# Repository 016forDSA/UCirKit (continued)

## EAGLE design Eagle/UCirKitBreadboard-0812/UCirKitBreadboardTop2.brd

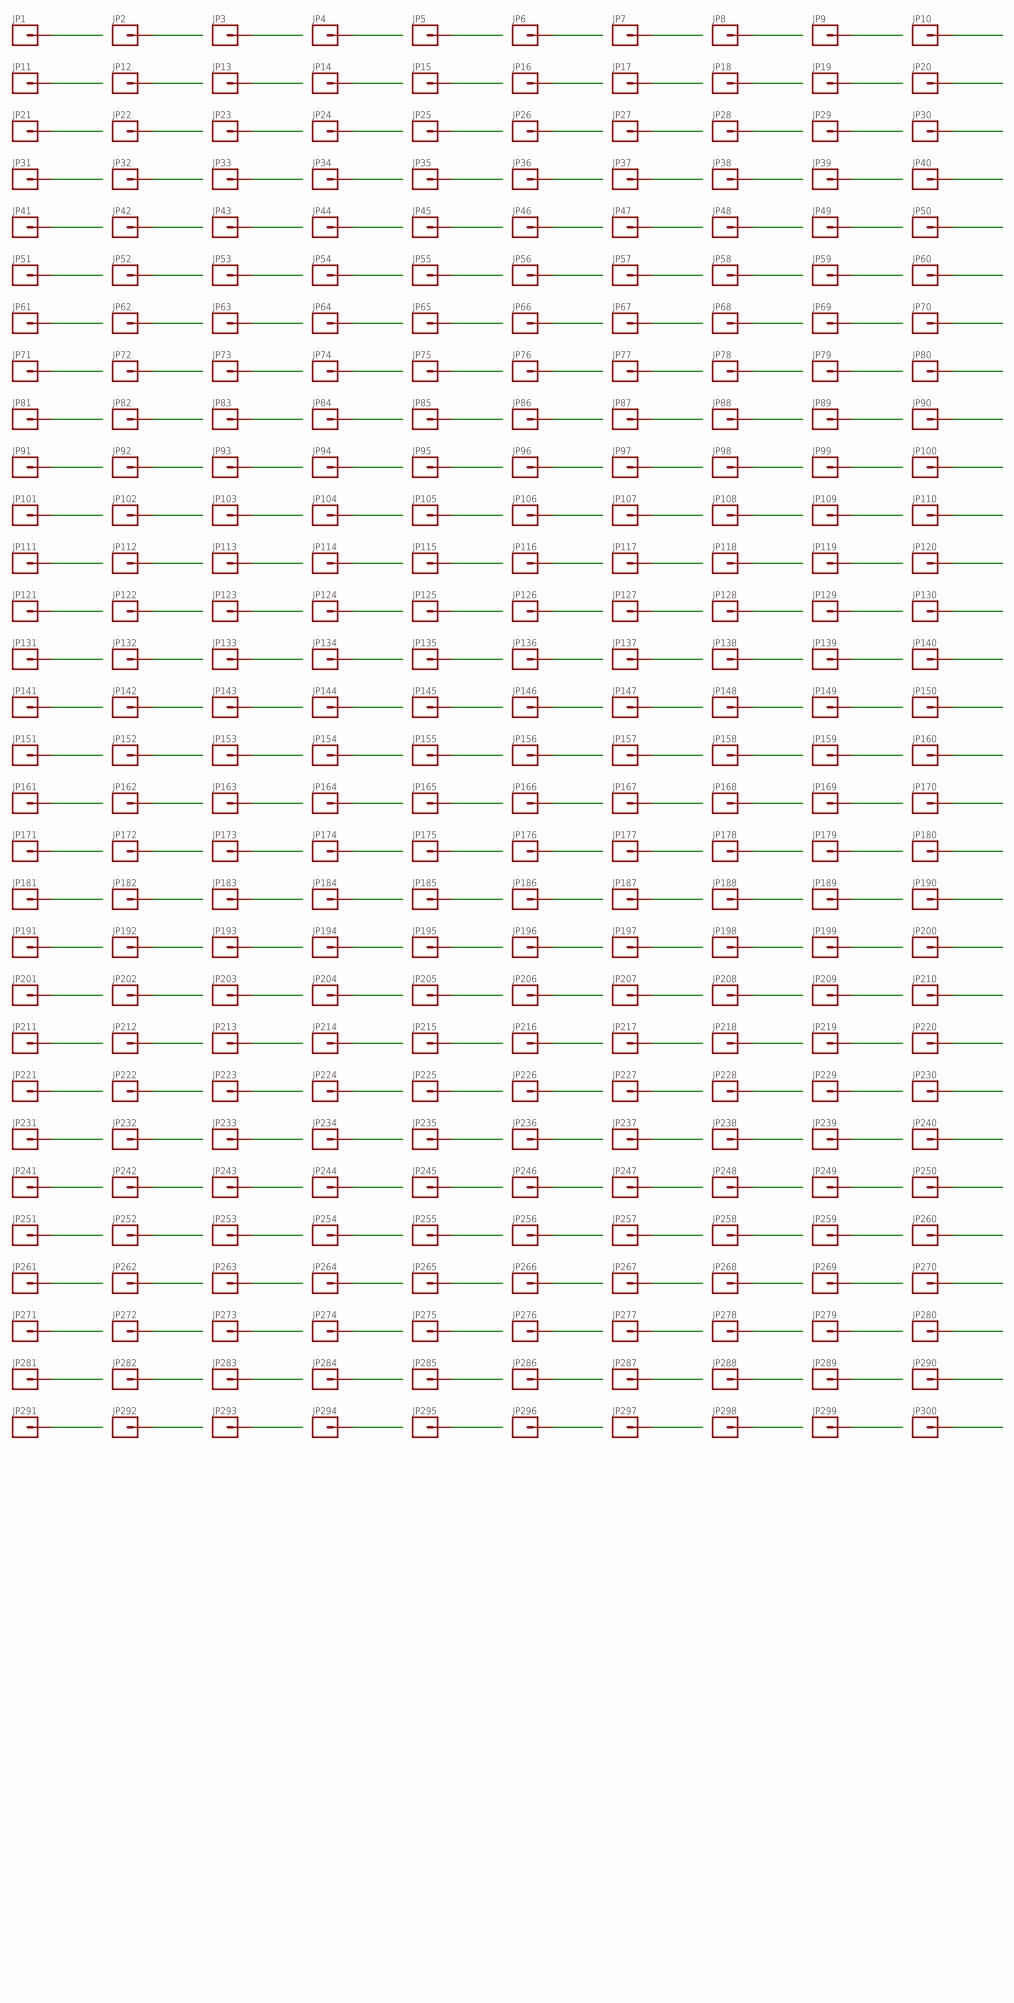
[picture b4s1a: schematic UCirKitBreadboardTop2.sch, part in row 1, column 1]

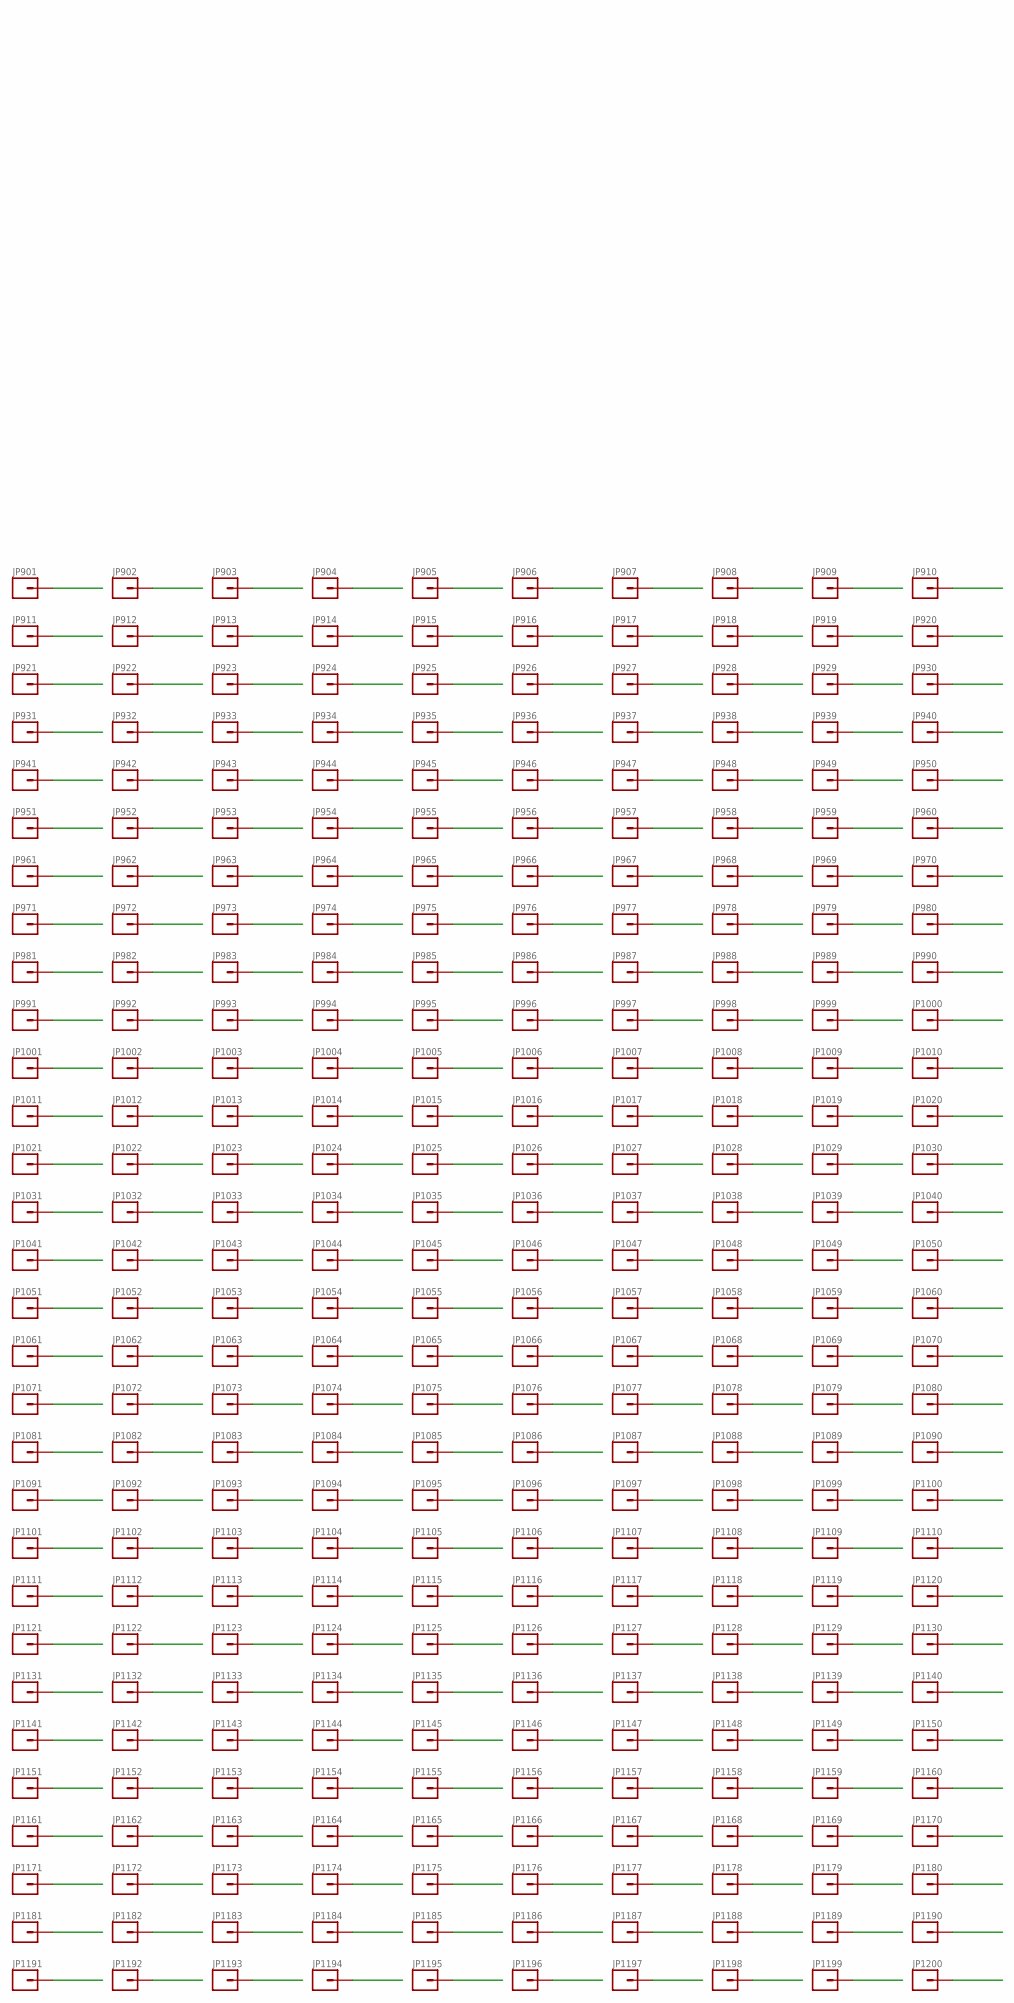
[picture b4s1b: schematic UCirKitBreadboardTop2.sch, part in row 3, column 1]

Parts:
JP1, JP2, JP3, JP4, JP5, JP6, JP7, JP8, JP9, JP10, JP11, JP12, JP13, JP14, JP15, JP16, JP17, JP18, JP19, JP20, JP21, JP22, JP23, JP24, JP25, JP26, JP27, JP28, JP29, JP30, JP31, JP32, JP33, JP34, JP35, JP36, JP37, JP38, JP39, JP40, JP41, JP42, JP43, JP44, JP45, JP46, JP47, JP48, JP49, JP50, JP51, JP52, JP53, JP54, JP55, JP56, JP57, JP58, JP59, JP60, JP61, JP62, JP63, JP64, JP65, JP66, JP67, JP68, JP69, JP70, JP71, JP72, JP73, JP74, JP75, JP76, JP77, JP78, JP79, JP80, JP81, JP82, JP83, JP84, JP85, JP86, JP87, JP88, JP89, JP90, JP91, JP92, JP93, JP94, JP95, JP96, JP97, JP98, JP99, JP100, JP101, JP102, JP103, JP104, JP105, JP106, JP107, JP108, JP109, JP110, JP111, JP112, JP113, JP114, JP115, JP116, JP117, JP118, JP119, JP120, JP121, JP122, JP123, JP124, JP125, JP126, JP127, JP128, JP129, JP130, JP131, JP132, JP133, JP134, JP135, JP136, JP137, JP138, JP139, JP140, JP141, JP142, JP143, JP144, JP145, JP146, JP147, JP148, JP149, JP150, JP151, JP152, JP153, JP154, JP155, JP156, JP157, JP158, JP159, JP160, JP161, JP162, JP163, JP164, JP165, JP166, JP167, JP168, JP169, JP170, JP171, JP172, JP173, JP174, JP175, JP176, JP177, JP178, JP179, JP180, JP181, JP182, JP183, JP184, JP185, JP186, JP187, JP188, JP189, JP190, JP191, JP192, JP193, JP194, JP195, JP196, JP197, JP198, JP199, JP200, JP201, JP202, JP203, JP204, JP205, JP206, JP207, JP208, JP209, JP210, JP211, JP212, JP213, JP214, JP215, JP216, JP217, JP218, JP219, JP220, JP221, JP222, JP223, JP224, JP225, JP226, JP227, JP228, JP229, JP230, JP231, JP232, JP233, JP234, JP235, JP236, JP237, JP238, JP239, JP240, JP241, JP242, JP243, JP244, JP245, JP246, JP247, JP248, JP249, JP250, JP251, JP252, JP253, JP254, JP255, JP256, JP257, JP258, JP259, JP260, JP261, JP262, JP263, JP264, JP265, JP266, JP267, JP268, JP269, JP270, JP271, JP272, JP273, JP274, JP275, JP276, JP277, JP278, JP279, JP280, JP281, JP282, JP283, JP284, JP285, JP286, JP287, JP288, JP289, JP290, JP291, JP292, JP293, JP294, JP295, JP296, JP297, JP298, JP299, JP300: M01PTH_WITHOUT_TEXT; 1X01_WITHOUT_TEXT
JP901, JP902, JP903, JP904, JP905, JP906, JP907, JP908, JP909, JP910, JP911, JP912, JP913, JP914, JP915, JP916, JP917, JP918, JP919, JP920, JP921, JP922, JP923, JP924, JP925, JP926, JP927, JP928, JP929, JP930, JP931, JP932, JP933, JP934, JP935, JP936, JP937, JP938, JP939, JP940, JP941, JP942, JP943, JP944, JP945, JP946, JP947, JP948, JP949, JP950, JP951, JP952, JP953, JP954, JP955, JP956, JP957, JP958, JP959, JP960, JP961, JP962, JP963, JP964, JP965, JP966, JP967, JP968, JP969, JP970, JP971, JP972, JP973, JP974, JP975, JP976, JP977, JP978, JP979, JP980, JP981, JP982, JP983, JP984, JP985, JP986, JP987, JP988, JP989, JP990, JP991, JP992, JP993, JP994, JP995, JP996, JP997, JP998, JP999, JP1000, JP1001, JP1002, JP1003, JP1004, JP1005, JP1006, JP1007, JP1008, JP1009, JP1010, JP1011, JP1012, JP1013, JP1014, JP1015, JP1016, JP1017, JP1018, JP1019, JP1020, JP1021, JP1022, JP1023, JP1024, JP1025, JP1026, JP1027, JP1028, JP1029, JP1030, JP1031, JP1032, JP1033, JP1034, JP1035, JP1036, JP1037, JP1038, JP1039, JP1040, JP1041, JP1042, JP1043, JP1044, JP1045, JP1046, JP1047, JP1048, JP1049, JP1050, JP1051, JP1052, JP1053, JP1054, JP1055, JP1056, JP1057, JP1058, JP1059, JP1060, JP1061, JP1062, JP1063, JP1064, JP1065, JP1066, JP1067, JP1068, JP1069, JP1070, JP1071, JP1072, JP1073, JP1074, JP1075, JP1076, JP1077, JP1078, JP1079, JP1080, JP1081, JP1082, JP1083, JP1084, JP1085, JP1086, JP1087, JP1088, JP1089, JP1090, JP1091, JP1092, JP1093, JP1094, JP1095, JP1096, JP1097, JP1098, JP1099, JP1100, JP1101, JP1102, JP1103, JP1104, JP1105, JP1106, JP1107, JP1108, JP1109, JP1110, JP1111, JP1112, JP1113, JP1114, JP1115, JP1116, JP1117, JP1118, JP1119, JP1120, JP1121, JP1122, JP1123, JP1124, JP1125, JP1126, JP1127, JP1128, JP1129, JP1130, JP1131, JP1132, JP1133, JP1134, JP1135, JP1136, JP1137, JP1138, JP1139, JP1140, JP1141, JP1142, JP1143, JP1144, JP1145, JP1146, JP1147, JP1148, JP1149, JP1150, JP1151, JP1152, JP1153, JP1154, JP1155, JP1156, JP1157, JP1158, JP1159, JP1160, JP1161, JP1162, JP1163, JP1164, JP1165, JP1166, JP1167, JP1168, JP1169, JP1170, JP1171, JP1172, JP1173, JP1174, JP1175, JP1176, JP1177, JP1178, JP1179, JP1180, JP1181, JP1182, JP1183, JP1184, JP1185, JP1186, JP1187, JP1188, JP1189, JP1190, JP1191, JP1192, JP1193, JP1194, JP1195, JP1196, JP1197, JP1198, JP1199, JP1200: M01PTH_SMD_1.27X0.635MM_NO_SILK; 1X01_SMD_1.27X0.635MM_NO_SILK

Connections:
NEW_0: JP10.1, JP1021.P$2
NEW_1: JP7.1, JP1081.P$2
NEW_2: JP8.1, JP1022.P$2
NEW_3: JP9.1, JP1082.P$2
NEW_4: JP20.1, JP1023.P$2
NEW_5: JP18.1, JP1083.P$2
NEW_6: JP19.1, JP1024.P$2
NEW_7: JP17.1, JP1084.P$2
NEW_8: JP30.1, JP1025.P$2
NEW_9: JP29.1, JP1085.P$2
NEW_10: JP28.1, JP1026.P$2
NEW_11: JP27.1, JP1086.P$2
NEW_12: JP40.1, JP1027.P$2
NEW_13: JP39.1, JP1087.P$2
NEW_14: JP37.1, JP1028.P$2
NEW_15: JP38.1, JP1088.P$2
NEW_16: JP50.1, JP1029.P$2
NEW_17: JP49.1, JP1089.P$2
NEW_18: JP48.1, JP1030.P$2
NEW_19: JP47.1, JP1090.P$2
NEW_20: JP60.1, JP1031.P$2
NEW_21: JP59.1, JP1091.P$2
NEW_22: JP58.1, JP1032.P$2
NEW_23: JP57.1, JP1092.P$2
NEW_24: JP68.1, JP1033.P$2
NEW_25: JP67.1, JP1093.P$2
NEW_26: JP70.1, JP1034.P$2
NEW_27: JP69.1, JP1094.P$2
NEW_28: JP78.1, JP1035.P$2
NEW_29: JP77.1, JP1095.P$2
NEW_30: JP80.1, JP1036.P$2
NEW_31: JP79.1, JP1096.P$2
NEW_32: JP88.1, JP1037.P$2
NEW_33: JP87.1, JP1097.P$2
NEW_34: JP90.1, JP1038.P$2
NEW_35: JP89.1, JP1098.P$2
NEW_36: JP98.1, JP1039.P$2
NEW_37: JP97.1, JP1099.P$2
NEW_38: JP100.1, JP1040.P$2
NEW_39: JP99.1, JP1100.P$2
NEW_40: JP108.1, JP1041.P$2
NEW_41: JP107.1, JP1101.P$2
NEW_42: JP110.1, JP1042.P$2
NEW_43: JP109.1, JP1102.P$2
NEW_44: JP118.1, JP1043.P$2
NEW_45: JP117.1, JP1103.P$2
NEW_46: JP120.1, JP1044.P$2
NEW_47: JP119.1, JP1104.P$2
NEW_48: JP128.1, JP1045.P$2
NEW_49: JP127.1, JP1105.P$2
NEW_50: JP130.1, JP1046.P$2
NEW_51: JP129.1, JP1106.P$2
NEW_52: JP138.1, JP1047.P$2
NEW_53: JP137.1, JP1107.P$2
NEW_54: JP140.1, JP1048.P$2
NEW_55: JP139.1, JP1108.P$2
NEW_56: JP148.1, JP1049.P$2
NEW_57: JP147.1, JP1109.P$2
NEW_58: JP150.1, JP1050.P$2
NEW_59: JP149.1, JP1110.P$2
NEW_60: JP158.1, JP1051.P$2
NEW_61: JP157.1, JP1111.P$2
NEW_62: JP160.1, JP1052.P$2
NEW_63: JP159.1, JP1112.P$2
NEW_64: JP168.1, JP1053.P$2
NEW_65: JP167.1, JP1113.P$2
NEW_66: JP170.1, JP1054.P$2
NEW_67: JP169.1, JP1114.P$2
NEW_68: JP178.1, JP1055.P$2
NEW_69: JP177.1, JP1115.P$2
NEW_70: JP180.1, JP1056.P$2
NEW_71: JP179.1, JP1116.P$2
NEW_72: JP188.1, JP1057.P$2
NEW_73: JP187.1, JP1117.P$2
NEW_74: JP190.1, JP1058.P$2
NEW_75: JP189.1, JP1118.P$2
NEW_76: JP198.1, JP1059.P$2
NEW_77: JP248.1, JP1119.P$2
NEW_78: JP197.1, JP1060.P$2
NEW_79: JP258.1, JP1120.P$2
NEW_80: JP208.1, JP1061.P$2
NEW_81: JP257.1, JP1121.P$2
NEW_82: JP207.1, JP1062.P$2
NEW_83: JP268.1, JP1122.P$2
NEW_84: JP218.1, JP1063.P$2
NEW_85: JP267.1, JP1123.P$2
NEW_86: JP217.1, JP1064.P$2
NEW_87: JP278.1, JP1124.P$2
NEW_88: JP228.1, JP1065.P$2
NEW_89: JP277.1, JP1125.P$2
NEW_90: JP227.1, JP1066.P$2
NEW_91: JP287.1, JP1126.P$2
NEW_92: JP238.1, JP1067.P$2
NEW_93: JP290.1, JP1127.P$2
NEW_94: JP237.1, JP1068.P$2
NEW_95: JP297.1, JP1128.P$2
NEW_96: JP247.1, JP1069.P$2
NEW_97: JP300.1, JP1129.P$2
NEW_98: JP250.1, JP1070.P$2
NEW_99: JP249.1, JP1130.P$2
NEW_100: JP260.1, JP1071.P$2
NEW_101: JP240.1, JP1131.P$2
NEW_102: JP259.1, JP1072.P$2
NEW_103: JP239.1, JP1132.P$2
NEW_104: JP270.1, JP1073.P$2
NEW_105: JP230.1, JP1133.P$2
NEW_106: JP269.1, JP1074.P$2
NEW_107: JP229.1, JP1134.P$2
NEW_108: JP280.1, JP1075.P$2
NEW_109: JP220.1, JP1135.P$2
NEW_110: JP279.1, JP1076.P$2
NEW_111: JP219.1, JP1136.P$2
NEW_112: JP289.1, JP1077.P$2
NEW_113: JP210.1, JP1137.P$2
NEW_114: JP288.1, JP1078.P$2
NEW_115: JP209.1, JP1138.P$2
NEW_116: JP299.1, JP1079.P$2
NEW_117: JP200.1, JP1139.P$2
NEW_118: JP298.1, JP1080.P$2
NEW_119: JP199.1, JP1140.P$2
NEW_120: JP1.1, JP961.P$2
NEW_121: JP2.1, JP901.P$2
NEW_122: JP3.1, JP962.P$2
NEW_123: JP4.1, JP902.P$2
NEW_124: JP11.1, JP963.P$2
NEW_125: JP13.1, JP903.P$2
NEW_126: JP14.1, JP964.P$2
NEW_127: JP12.1, JP904.P$2
NEW_128: JP21.1, JP965.P$2
NEW_129: JP22.1, JP905.P$2
NEW_130: JP24.1, JP966.P$2
NEW_131: JP23.1, JP906.P$2
NEW_132: JP31.1, JP967.P$2
NEW_133: JP32.1, JP907.P$2
NEW_134: JP33.1, JP968.P$2
NEW_135: JP34.1, JP908.P$2
NEW_136: JP41.1, JP969.P$2
NEW_137: JP42.1, JP909.P$2
NEW_138: JP43.1, JP970.P$2
NEW_139: JP44.1, JP910.P$2
NEW_140: JP51.1, JP971.P$2
NEW_141: JP52.1, JP911.P$2
NEW_142: JP54.1, JP972.P$2
NEW_143: JP53.1, JP912.P$2
NEW_144: JP63.1, JP973.P$2
NEW_145: JP64.1, JP913.P$2
NEW_146: JP61.1, JP974.P$2
NEW_147: JP62.1, JP914.P$2
NEW_148: JP73.1, JP975.P$2
NEW_149: JP74.1, JP915.P$2
NEW_150: JP71.1, JP976.P$2
NEW_151: JP72.1, JP916.P$2
NEW_152: JP83.1, JP977.P$2
NEW_153: JP84.1, JP917.P$2
NEW_154: JP81.1, JP978.P$2
NEW_155: JP82.1, JP918.P$2
NEW_156: JP93.1, JP979.P$2
NEW_157: JP94.1, JP919.P$2
NEW_158: JP91.1, JP980.P$2
NEW_159: JP92.1, JP920.P$2
NEW_160: JP103.1, JP981.P$2
NEW_161: JP104.1, JP921.P$2
NEW_162: JP101.1, JP982.P$2
NEW_163: JP102.1, JP922.P$2
NEW_164: JP113.1, JP983.P$2
NEW_165: JP114.1, JP923.P$2
NEW_166: JP111.1, JP984.P$2
NEW_167: JP112.1, JP924.P$2
NEW_168: JP123.1, JP985.P$2
NEW_169: JP124.1, JP925.P$2
NEW_170: JP121.1, JP986.P$2
NEW_171: JP122.1, JP926.P$2
NEW_172: JP133.1, JP987.P$2
NEW_173: JP134.1, JP927.P$2
NEW_174: JP131.1, JP988.P$2
NEW_175: JP132.1, JP928.P$2
NEW_176: JP143.1, JP989.P$2
NEW_177: JP144.1, JP929.P$2
NEW_178: JP141.1, JP990.P$2
NEW_179: JP142.1, JP930.P$2
NEW_180: JP153.1, JP991.P$2
NEW_181: JP154.1, JP931.P$2
NEW_182: JP151.1, JP992.P$2
NEW_183: JP152.1, JP932.P$2
NEW_184: JP163.1, JP993.P$2
NEW_185: JP164.1, JP933.P$2
NEW_186: JP161.1, JP994.P$2
NEW_187: JP162.1, JP934.P$2
NEW_188: JP173.1, JP995.P$2
NEW_189: JP174.1, JP935.P$2
NEW_190: JP171.1, JP996.P$2
NEW_191: JP172.1, JP936.P$2
NEW_192: JP183.1, JP997.P$2
NEW_193: JP243.1, JP937.P$2
NEW_194: JP184.1, JP998.P$2
NEW_195: JP244.1, JP938.P$2
NEW_196: JP193.1, JP999.P$2
NEW_197: JP253.1, JP939.P$2
NEW_198: JP194.1, JP1000.P$2
NEW_199: JP254.1, JP940.P$2
NEW_200: JP203.1, JP1001.P$2
NEW_201: JP264.1, JP941.P$2
NEW_202: JP204.1, JP1002.P$2
NEW_203: JP263.1, JP942.P$2
NEW_204: JP213.1, JP1003.P$2
NEW_205: JP273.1, JP943.P$2
NEW_206: JP214.1, JP1004.P$2
NEW_207: JP274.1, JP944.P$2
NEW_208: JP223.1, JP1005.P$2
NEW_209: JP284.1, JP945.P$2
NEW_210: JP224.1, JP1006.P$2
NEW_211: JP281.1, JP946.P$2
NEW_212: JP233.1, JP1007.P$2
NEW_213: JP294.1, JP947.P$2
NEW_214: JP234.1, JP1008.P$2
NEW_215: JP291.1, JP948.P$2
NEW_216: JP241.1, JP1009.P$2
NEW_217: JP231.1, JP949.P$2
NEW_218: JP242.1, JP1010.P$2
NEW_219: JP232.1, JP950.P$2
NEW_220: JP251.1, JP1011.P$2
NEW_221: JP221.1, JP951.P$2
NEW_222: JP252.1, JP1012.P$2
NEW_223: JP222.1, JP952.P$2
NEW_224: JP261.1, JP1013.P$2
NEW_225: JP211.1, JP953.P$2
NEW_226: JP262.1, JP1014.P$2
NEW_227: JP212.1, JP954.P$2
NEW_228: JP271.1, JP1015.P$2
NEW_229: JP201.1, JP955.P$2
NEW_230: JP272.1, JP1016.P$2
NEW_231: JP202.1, JP956.P$2
NEW_232: JP282.1, JP1017.P$2
NEW_233: JP191.1, JP957.P$2
NEW_234: JP283.1, JP1018.P$2
NEW_235: JP192.1, JP958.P$2
NEW_236: JP292.1, JP1019.P$2
NEW_237: JP181.1, JP959.P$2
NEW_238: JP293.1, JP1020.P$2
NEW_239: JP182.1, JP960.P$2
NEW_240: JP105.1, JP1141.P$2
NEW_241: JP115.1, JP1142.P$2
NEW_242: JP125.1, JP1143.P$2
NEW_243: JP135.1, JP1144.P$2
NEW_244: JP145.1, JP1145.P$2
NEW_245: JP155.1, JP1146.P$2
NEW_246: JP165.1, JP1147.P$2
NEW_247: JP175.1, JP1148.P$2
NEW_248: JP185.1, JP1149.P$2
NEW_249: JP195.1, JP1150.P$2
NEW_250: JP5.1, JP1151.P$2
NEW_251: JP15.1, JP1152.P$2
NEW_252: JP25.1, JP1153.P$2
NEW_253: JP35.1, JP1154.P$2
NEW_254: JP45.1, JP1155.P$2
NEW_255: JP55.1, JP1156.P$2
NEW_256: JP65.1, JP1157.P$2
NEW_257: JP75.1, JP1158.P$2
NEW_258: JP85.1, JP1159.P$2
NEW_259: JP95.1, JP1160.P$2
NEW_260: JP295.1, JP1181.P$2
NEW_261: JP285.1, JP1182.P$2
NEW_262: JP275.1, JP1183.P$2
NEW_263: JP265.1, JP1184.P$2
NEW_264: JP255.1, JP1185.P$2
NEW_265: JP245.1, JP1186.P$2
NEW_266: JP235.1, JP1187.P$2
NEW_267: JP225.1, JP1188.P$2
NEW_268: JP215.1, JP1189.P$2
NEW_269: JP205.1, JP1190.P$2
NEW_270: JP196.1, JP1161.P$2
NEW_271: JP186.1, JP1162.P$2
NEW_272: JP176.1, JP1163.P$2
NEW_273: JP166.1, JP1164.P$2
NEW_274: JP156.1, JP1165.P$2
NEW_275: JP146.1, JP1166.P$2
NEW_276: JP136.1, JP1167.P$2
NEW_277: JP126.1, JP1168.P$2
NEW_278: JP116.1, JP1169.P$2
NEW_279: JP106.1, JP1170.P$2
NEW_280: JP96.1, JP1171.P$2
NEW_281: JP86.1, JP1172.P$2
NEW_282: JP76.1, JP1173.P$2
NEW_283: JP66.1, JP1174.P$2
NEW_284: JP56.1, JP1175.P$2
NEW_285: JP46.1, JP1176.P$2
NEW_286: JP36.1, JP1177.P$2
NEW_287: JP26.1, JP1178.P$2
NEW_288: JP16.1, JP1179.P$2
NEW_289: JP6.1, JP1180.P$2
NEW_290: JP206.1, JP1191.P$2
NEW_291: JP216.1, JP1192.P$2
NEW_292: JP226.1, JP1193.P$2
NEW_293: JP236.1, JP1194.P$2
NEW_294: JP246.1, JP1195.P$2
NEW_295: JP256.1, JP1196.P$2
NEW_296: JP266.1, JP1197.P$2
NEW_297: JP276.1, JP1198.P$2
NEW_298: JP286.1, JP1199.P$2
NEW_299: JP296.1, JP1200.P$2

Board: 4 copper layers, 600 parts (300 on the bottom side), 300 nets, no tracks yet.
